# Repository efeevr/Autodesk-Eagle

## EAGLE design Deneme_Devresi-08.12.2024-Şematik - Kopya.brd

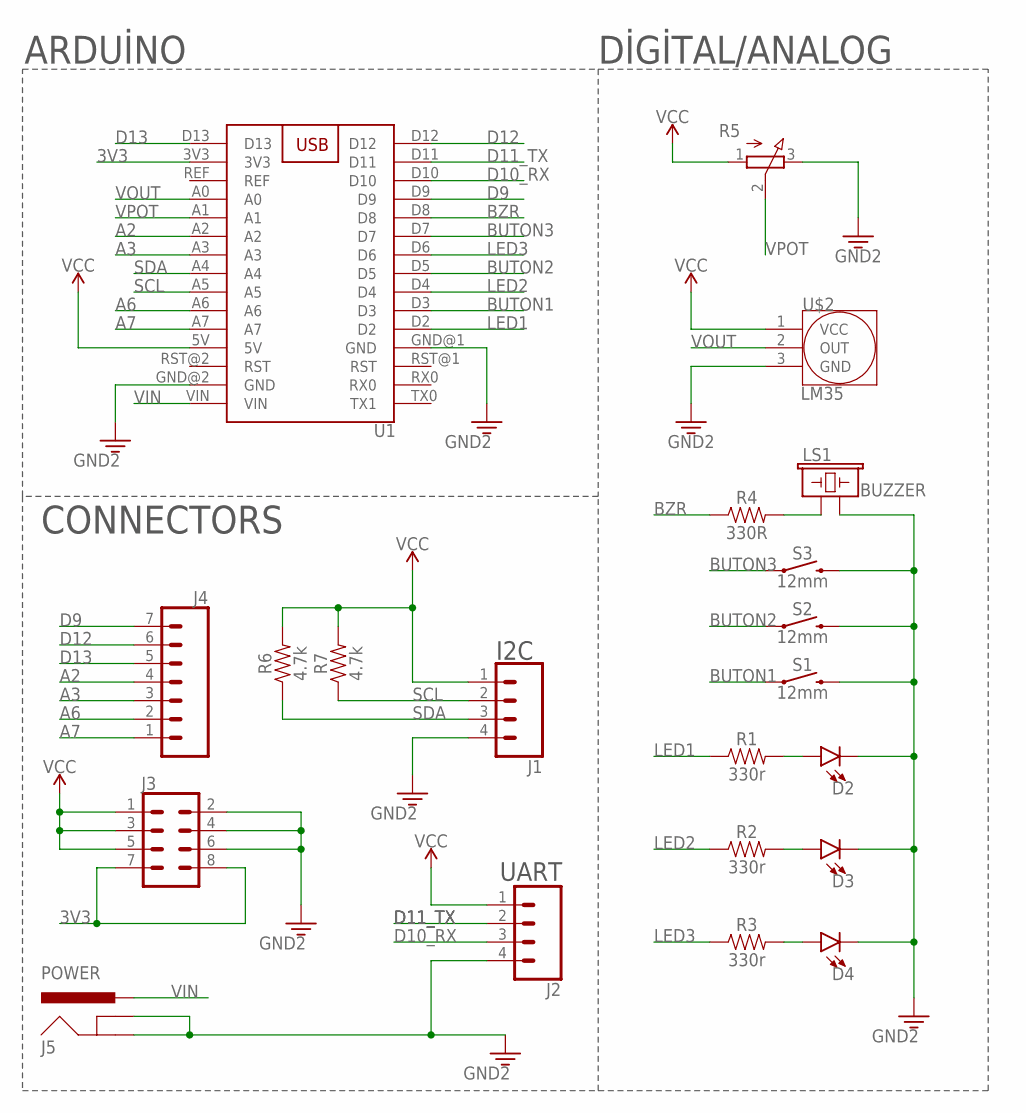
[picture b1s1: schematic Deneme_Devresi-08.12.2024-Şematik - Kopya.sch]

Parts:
D2, D3, D4: LED-3MM-NO_SILK; LED_3MM-NS
J1, J2: CONN_04JST-PTH; JST-4-PTH
J3: CONN_04X2; 2X4
J4: CONN_07NO_SILK; 1X07_NO_SILK
J5: POWER; POWER_JACK_PTH_SLOT_NO_OVRHNG_SILK
LS1: BUZZER; BUZZER-12MM-NS
R1, R2, R3: 330r; AXIAL-0.3
R4: 330R; AXIAL-0.3
R5: 3RP/1610N
R6, R7: 4.7k; AXIAL-0.3
S1, S2, S3: 12mm; TACTILE_SWITCH_PTH_12MM
U1: ARDUINO_NANO
U$2: LM35; TO-92

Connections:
3V3: J3.7, J3.8, U1.3V3
A2: J4.4, U1.A2
A3: J4.3, U1.A3
A6: J4.2, U1.A6
A7: J4.1, U1.A7
BUTON1: S1.1, U1.D3
BUTON2: S2.1, U1.D5
BUTON3: S3.1, U1.D7
BZR: R4.P$1 (1), U1.D8
D9: J4.7, U1.D9
D10_RX: J2.3, U1.D10
D11_TX: J2.2, U1.D11
D12: J4.6, U1.D12
D13: J4.5, U1.D13
GND: D2.K (C), D3.K (C), D4.K (C), J1.4, J2.4, J3.2, J3.4, J3.6, J5.GND, J5.GNDBREAK, LS1.- (2), R5.3 (E), S1.3 (2), S2.3 (2), S3.3 (2), U1.GND@1 (GND), U1.GND@2 (GND), U$2.3 (GND)
LED1: R1.P$1 (1), U1.D2
LED2: R2.P$1 (1), U1.D4
LED3: R3.P$1 (1), U1.D6
unnamed: LS1.+ (1), R4.P$2 (2)
unnamed: D4.A, R3.P$2 (2)
unnamed: D3.A, R2.P$2 (2)
unnamed: D2.A, R1.P$2 (2)
SCL: J1.2, R7.P$1 (1), U1.A5
SDA: J1.3, R6.P$1 (1), U1.A4
VCC: J1.1, J2.1, J3.1, J3.3, J3.5, R5.1 (A), R6.P$2 (2), R7.P$2 (2), U1.5V, U$2.1 (VCC)
VIN: J5.PWR, U1.VIN
VOUT: U1.A0, U$2.2 (OUT)
VPOT: R5.2 (S), U1.A1

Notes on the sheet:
ARDUİNO
CONNECTORS
DİGİTAL/ANALOG
UART
I2C

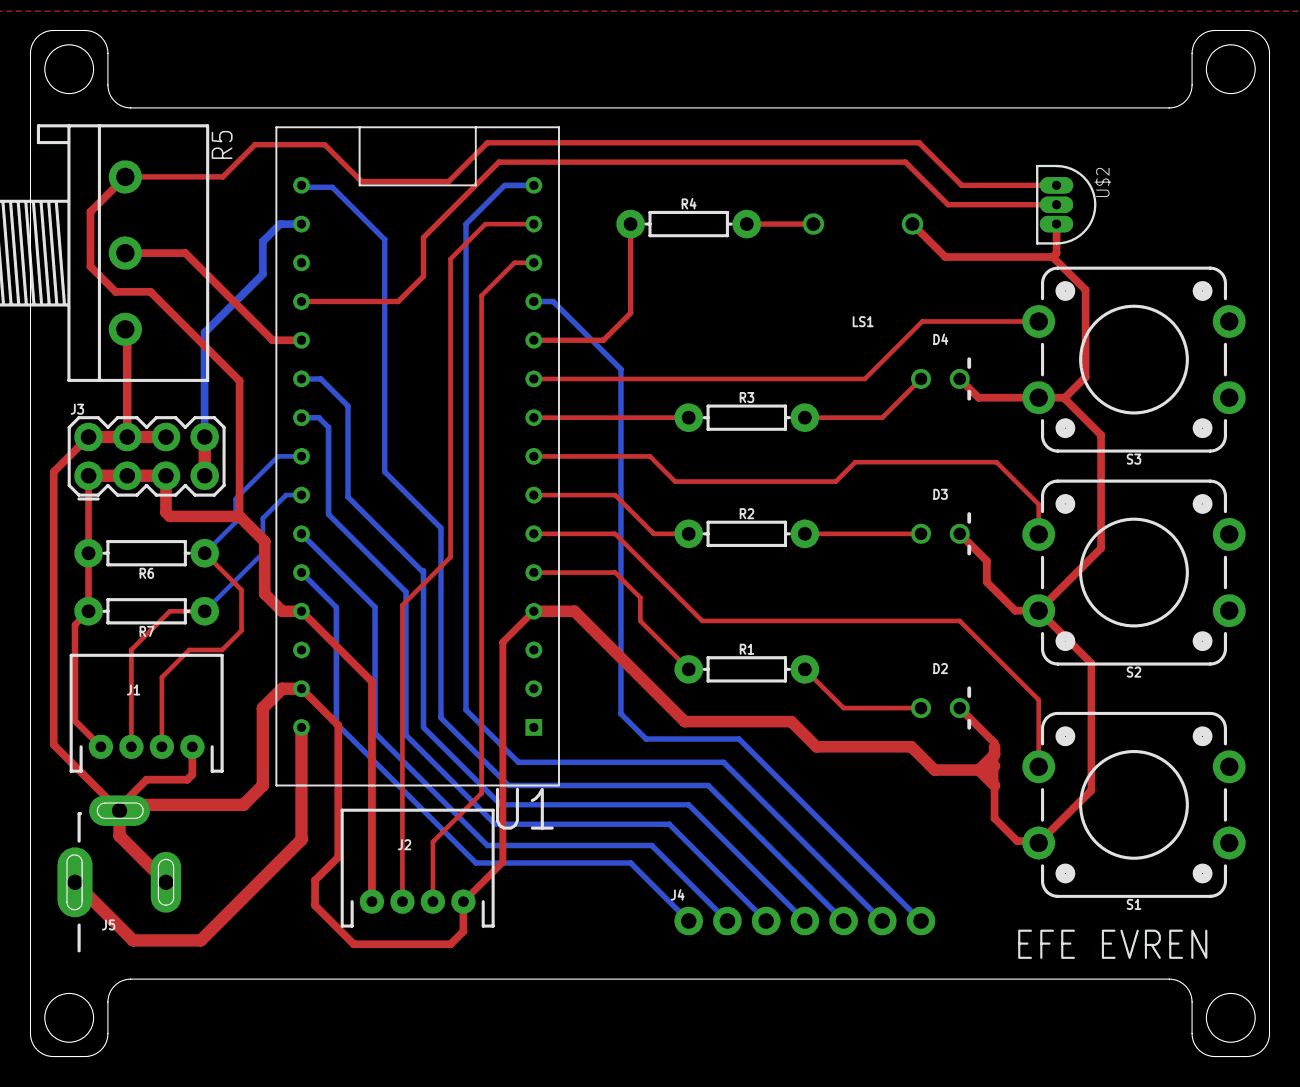
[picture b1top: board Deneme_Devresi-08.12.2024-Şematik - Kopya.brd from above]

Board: 2 copper layers, 81.3 x 67.3 mm, 21 parts (0 on the bottom side), 28 nets.

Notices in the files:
parts and their libraries:
SparkFun-LED: Licensing: Creative Commons ShareAlike 4.0 International - https://creativecommons.org/licenses/by-sa/4.0
